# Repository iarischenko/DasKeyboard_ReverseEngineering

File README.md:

# Das Keyboard Model S

CST-104-DAS_Mother PCB  reverse engineering:\
- layout is the same as in original board, the original CST-104-DAS_Daughter
PCB Ver 1.5 could be used
- added hotswap Kailh sockets

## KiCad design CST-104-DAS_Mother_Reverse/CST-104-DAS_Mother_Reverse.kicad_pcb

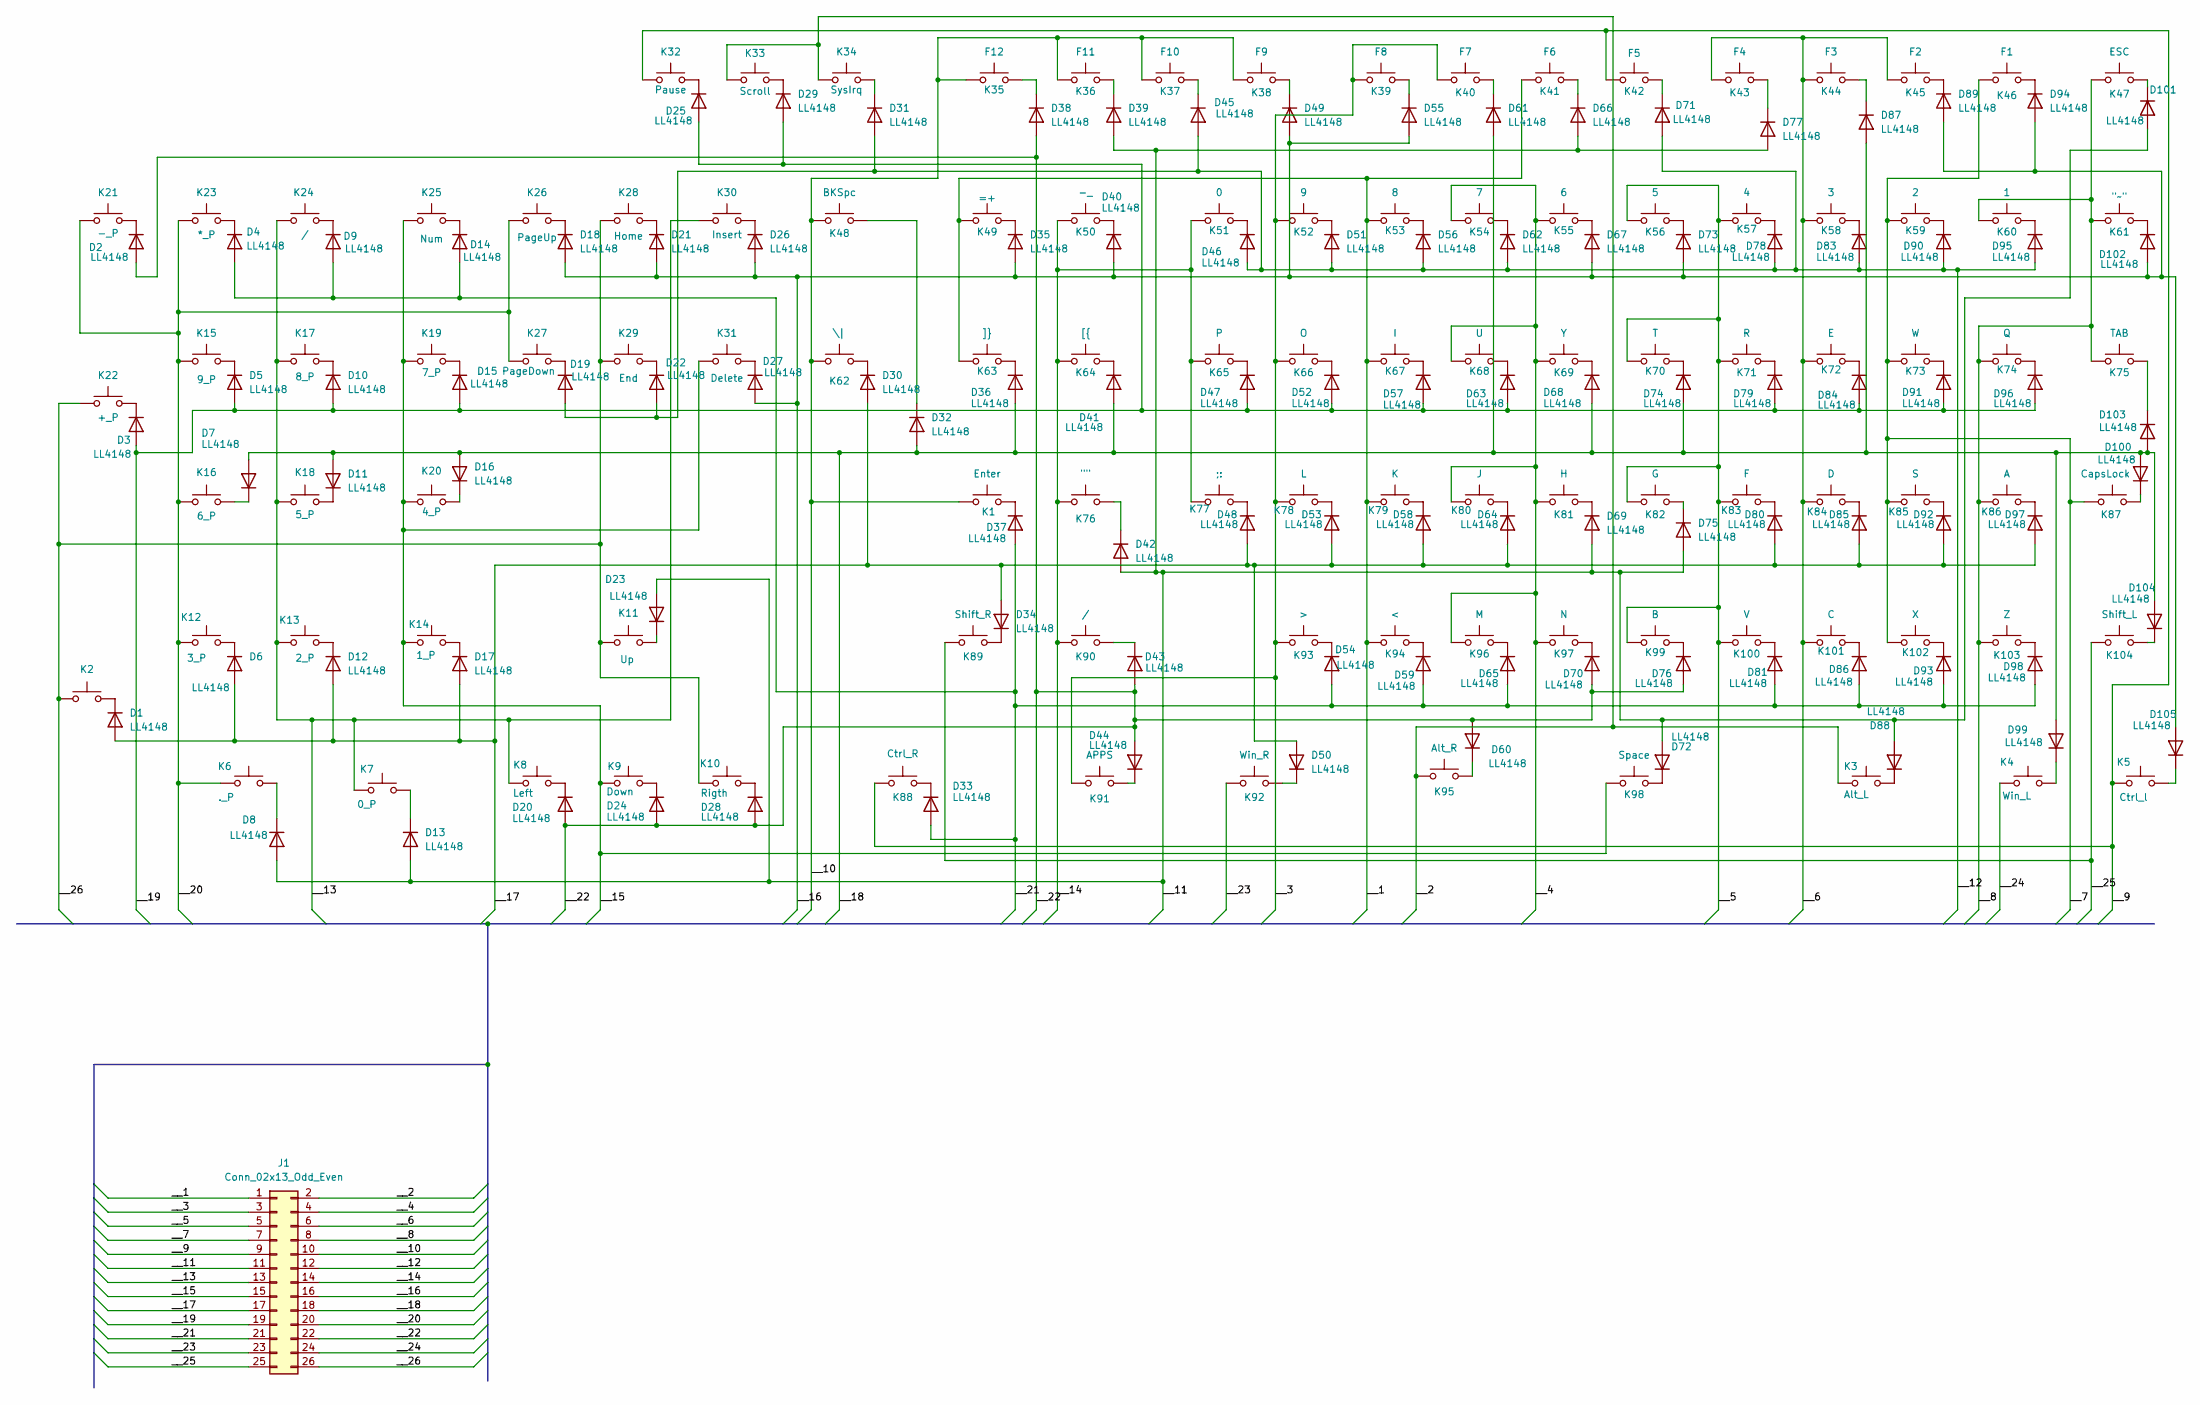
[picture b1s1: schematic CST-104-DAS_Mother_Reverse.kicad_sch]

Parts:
D1, D2, D3, D4, D5, D6, D7, D8, D9, D10, D11, D12, D13, D14, D15, D16, D17, D18, D19, D20, D21, D22, D23, D24, D25, D26, D27, D28, D29, D30, D31, D32, D33, D34, D35, D36, D37, D38, D39, D40, D41, D42, D43, D44, D45, D46, D47, D48, D49, D50, D51, D52, D53, D54, D55, D56, D57, D58, D59, D60, D61, D62, D63, D64, D65, D66, D67, D68, D69, D70, D71, D72, D73, D74, D75, D76, D77, D78, D79, D80, D81, D83, D84, D85, D86, D87, D88, D89, D90, D91, D92, D93, D94, D95, D96, D97, D98, D99, D100, D101, D102, D103, D104, D105: LL4148; D_MiniMELF
J1: Conn_02x13_Odd_Even; PinSocket_2x13_P2.54mm_Vertical
K1: Enter; SW_Hotswap_Kailh_MX
K2: Enter_P; SW_Hotswap_Kailh_MX
K3: Alt_L; SW_Hotswap_Kailh_MX
K4: Win_L; SW_Hotswap_Kailh_MX
K5: Ctrl_l; SW_Hotswap_Kailh_MX
K6: ._P; SW_Hotswap_Kailh_MX
K7: 0_P; SW_Hotswap_Kailh_MX
K8: Left; SW_Hotswap_Kailh_MX
K9: Down; SW_Hotswap_Kailh_MX
K10: Rigth; SW_Hotswap_Kailh_MX
K11: Up; SW_Hotswap_Kailh_MX
K12: 3_P; SW_Hotswap_Kailh_MX
K13: 2_P; SW_Hotswap_Kailh_MX
K14: 1_P; SW_Hotswap_Kailh_MX
K15: 9_P; SW_Hotswap_Kailh_MX
K16: 6_P; SW_Hotswap_Kailh_MX
K17: 8_P; SW_Hotswap_Kailh_MX
K18: 5_P; SW_Hotswap_Kailh_MX
K19: 7_P; SW_Hotswap_Kailh_MX
K20: 4_P; SW_Hotswap_Kailh_MX
K21: -_P; SW_Hotswap_Kailh_MX
K22: +_P; SW_Hotswap_Kailh_MX
K23: *_P; SW_Hotswap_Kailh_MX
K24, K90: /; SW_Hotswap_Kailh_MX
K25: Num; SW_Hotswap_Kailh_MX
K26: PageUp; SW_Hotswap_Kailh_MX
K27: PageDown; SW_Hotswap_Kailh_MX
K28: Home; SW_Hotswap_Kailh_MX
K29: End; SW_Hotswap_Kailh_MX
K30: Insert; SW_Hotswap_Kailh_MX
K31: Delete; SW_Hotswap_Kailh_MX
K32: Pause; SW_Hotswap_Kailh_MX
K33: Scroll; SW_Hotswap_Kailh_MX
K34: SysIrq; SW_Hotswap_Kailh_MX
K35: F12; SW_Hotswap_Kailh_MX
K36: F11; SW_Hotswap_Kailh_MX
K37: F10; SW_Hotswap_Kailh_MX
K38: F9; SW_Hotswap_Kailh_MX
K39: F8; SW_Hotswap_Kailh_MX
K40: F7; SW_Hotswap_Kailh_MX
K41: F6; SW_Hotswap_Kailh_MX
K42: F5; SW_Hotswap_Kailh_MX
K43: F4; SW_Hotswap_Kailh_MX
K44: F3; SW_Hotswap_Kailh_MX
K45: F2; SW_Hotswap_Kailh_MX
K46: F1; SW_Hotswap_Kailh_MX
K47: ESC; SW_Hotswap_Kailh_MX
K48: BKSpc; SW_Hotswap_Kailh_MX
K49: =+; SW_Hotswap_Kailh_MX
K50: -_; SW_Hotswap_Kailh_MX
K51: 0; SW_Hotswap_Kailh_MX
K52: 9; SW_Hotswap_Kailh_MX
K53: 8; SW_Hotswap_Kailh_MX
K54: 7; SW_Hotswap_Kailh_MX
K55: 6; SW_Hotswap_Kailh_MX
K56: 5; SW_Hotswap_Kailh_MX
K57: 4; SW_Hotswap_Kailh_MX
K58: 3; SW_Hotswap_Kailh_MX
K59: 2; SW_Hotswap_Kailh_MX
K60: 1; SW_Hotswap_Kailh_MX
K61: "~"; SW_Hotswap_Kailh_MX
K62: \|; SW_Hotswap_Kailh_MX
K63: ]}; SW_Hotswap_Kailh_MX
K64: [{; SW_Hotswap_Kailh_MX
K65: P; SW_Hotswap_Kailh_MX
K66: O; SW_Hotswap_Kailh_MX
K67: I; SW_Hotswap_Kailh_MX
K68: U; SW_Hotswap_Kailh_MX
K69: Y; SW_Hotswap_Kailh_MX
K70: T; SW_Hotswap_Kailh_MX
K71: R; SW_Hotswap_Kailh_MX
K72: E; SW_Hotswap_Kailh_MX
K73: W; SW_Hotswap_Kailh_MX
K74: Q; SW_Hotswap_Kailh_MX
K75: TAB; SW_Hotswap_Kailh_MX
K76: ""; SW_Hotswap_Kailh_MX
K77: ;:; SW_Hotswap_Kailh_MX
K78: L; SW_Hotswap_Kailh_MX
K79: K; SW_Hotswap_Kailh_MX
K80: J; SW_Hotswap_Kailh_MX
K81: H; SW_Hotswap_Kailh_MX
K82: G; SW_Hotswap_Kailh_MX
K83: F; SW_Hotswap_Kailh_MX
K84: D; SW_Hotswap_Kailh_MX
K85: S; SW_Hotswap_Kailh_MX
K86: A; SW_Hotswap_Kailh_MX
K87: CapsLock; SW_Hotswap_Kailh_MX
K88: Ctrl_R; SW_Hotswap_Kailh_MX
K89: Shift_R; SW_Hotswap_Kailh_MX
K91: APPS; SW_Hotswap_Kailh_MX
K92: Win_R; SW_Hotswap_Kailh_MX
K93: >; SW_Hotswap_Kailh_MX
K94: <; SW_Hotswap_Kailh_MX
K95: Alt_R; SW_Hotswap_Kailh_MX
K96: M; SW_Hotswap_Kailh_MX
K97: N; SW_Hotswap_Kailh_MX
K98: Space; SW_Hotswap_Kailh_MX
K99: B; SW_Hotswap_Kailh_MX
K100: V; SW_Hotswap_Kailh_MX
K101: C; SW_Hotswap_Kailh_MX
K102: X; SW_Hotswap_Kailh_MX
K103: Z; SW_Hotswap_Kailh_MX
K104: Shift_L; SW_Hotswap_Kailh_MX

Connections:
/__1: J1.1, K41.1, K49.1, K53.1, K63.1, K67.1, K79.1, K94.1
/__2: J1.2, K3.1, K33.1, K34.1, K95.1
/__3: J1.3, K39.1, K40.1, K52.1, K66.1, K78.1, K91.1, K93.1
/__4: J1.4, K54.1, K55.1, K68.1, K69.1, K80.1, K81.1, K96.1, K97.1
/__5: J1.5, K56.1, K57.1, K70.1, K71.1, K82.1, K83.1, K99.1, K100.1
/__6: J1.6, K43.1, K44.1, K45.1, K58.1, K72.1, K84.1, K101.1
/__7: J1.7, K46.1, K59.1, K73.1, K85.1, K87.1, K102.1
/__8: J1.8, K47.1, K60.1, K61.1, K74.1, K75.1, K86.1, K103.1
/__9: J1.9, K5.1, K32.1, K42.1, K88.1
/__10: J1.10, K1.1, K35.1, K36.1, K37.1, K38.1, K48.1, K62.1
/__11: D8.2 (A), D13.2 (A), D23.2 (A), D39.2 (A), D42.2 (A), D66.2 (A), D69.2 (A), D72.2 (A), D75.2 (A), D77.2 (A), D88.2 (A), D101.2 (A), J1.11
/__12: D19.2 (A), D22.2 (A), D31.2 (A), D45.2 (A), D46.2 (A), D51.2 (A), D56.2 (A), D62.2 (A), D71.2 (A), D78.2 (A), D83.2 (A), D90.2 (A), D95.2 (A), J1.12
/__13: J1.13, K7.1, K8.1, K13.1, K17.1, K18.1, K24.1, K30.1
/__14: J1.14, K50.1, K51.1, K64.1, K65.1, K76.1, K77.1, K90.1
/__15: J1.15, K9.1, K14.1, K19.1, K20.1, K25.1, K31.1, K98.1
/__16: D18.2 (A), D21.2 (A), D26.2 (A), D27.2 (A), D35.2 (A), D40.2 (A), D49.2 (A), D55.2 (A), D67.2 (A), D73.2 (A), D89.2 (A), D94.2 (A), D102.2 (A), D105.2 (A), J1.16
/__17: D1.2 (A), D6.2 (A), D12.2 (A), D17.2 (A), D30.2 (A), D34.2 (A), D48.2 (A), D50.2 (A), D53.2 (A), D58.2 (A), D64.2 (A), D80.2 (A), D85.2 (A), D92.2 (A), D97.2 (A), J1.17
/__18: D7.2 (A), D11.2 (A), D16.2 (A), D32.2 (A), D36.2 (A), D41.2 (A), D61.2 (A), D68.2 (A), D74.2 (A), D87.2 (A), D99.2 (A), D100.2 (A), D103.2 (A), D104.2 (A), J1.18
/__19: D3.2 (A), D5.2 (A), D10.2 (A), D15.2 (A), D25.2 (A), D29.2 (A), D47.2 (A), D52.2 (A), D57.2 (A), D63.2 (A), D79.2 (A), D84.2 (A), D91.2 (A), D96.2 (A), J1.19
/__20: J1.20, K6.1, K12.1, K15.1, K16.1, K21.1, K23.1, K26.1, K27.1
/__21: D4.2 (A), D9.2 (A), D14.2 (A), D33.2 (A), D37.2 (A), D54.2 (A), D59.2 (A), D65.2 (A), D81.2 (A), D86.2 (A), D93.2 (A), D98.2 (A), J1.21
/__22: D2.2 (A), D20.2 (A), D24.2 (A), D28.2 (A), D38.2 (A), D43.2 (A), D44.2 (A), D60.2 (A), D70.2 (A), D76.2 (A), J1.22
/__23: J1.23, K92.1
/__24: J1.24, K4.1
/__25: J1.25, K89.1, K104.1
/__26: J1.26, K2.1, K10.1, K11.1, K22.1, K28.1, K29.1
unnamed: D1.1 (K), K2.2
unnamed: D2.1 (K), K21.2
unnamed: D3.1 (K), K22.2
unnamed: D4.1 (K), K23.2
unnamed: D5.1 (K), K15.2
unnamed: D6.1 (K), K12.2
unnamed: D7.1 (K), K16.2
unnamed: D8.1 (K), K6.2
unnamed: D9.1 (K), K24.2
unnamed: D10.1 (K), K17.2
unnamed: D11.1 (K), K18.2
unnamed: D12.1 (K), K13.2
unnamed: D13.1 (K), K7.2
unnamed: D14.1 (K), K25.2
unnamed: D15.1 (K), K19.2
unnamed: D16.1 (K), K20.2
unnamed: D17.1 (K), K14.2
unnamed: D18.1 (K), K26.2
unnamed: D19.1 (K), K27.2
unnamed: D20.1 (K), K8.2
unnamed: D21.1 (K), K28.2
unnamed: D22.1 (K), K29.2
unnamed: D23.1 (K), K11.2
unnamed: D24.1 (K), K9.2
unnamed: D25.1 (K), K32.2
unnamed: D26.1 (K), K30.2
unnamed: D27.1 (K), K31.2
unnamed: D28.1 (K), K10.2
unnamed: D29.1 (K), K33.2
unnamed: D30.1 (K), K62.2
unnamed: D31.1 (K), K34.2
unnamed: D32.1 (K), K48.2
unnamed: D33.1 (K), K88.2
unnamed: D34.1 (K), K89.2
unnamed: D35.1 (K), K49.2
unnamed: D36.1 (K), K63.2
unnamed: D37.1 (K), K1.2
unnamed: D38.1 (K), K35.2
unnamed: D39.1 (K), K36.2
unnamed: D40.1 (K), K50.2
unnamed: D41.1 (K), K64.2
unnamed: D42.1 (K), K76.2
unnamed: D43.1 (K), K90.2
unnamed: D44.1 (K), K91.2
unnamed: D45.1 (K), K37.2
unnamed: D46.1 (K), K51.2
unnamed: D47.1 (K), K65.2
unnamed: D48.1 (K), K77.2
unnamed: D49.1 (K), K38.2
unnamed: D50.1 (K), K92.2
unnamed: D51.1 (K), K52.2
unnamed: D52.1 (K), K66.2
unnamed: D53.1 (K), K78.2
unnamed: D54.1 (K), K93.2
unnamed: D55.1 (K), K39.2
unnamed: D56.1 (K), K53.2
unnamed: D57.1 (K), K67.2
unnamed: D58.1 (K), K79.2
unnamed: D59.1 (K), K94.2
unnamed: D60.1 (K), K95.2
unnamed: D61.1 (K), K40.2
unnamed: D62.1 (K), K54.2
unnamed: D63.1 (K), K68.2
unnamed: D64.1 (K), K80.2
unnamed: D65.1 (K), K96.2
unnamed: D66.1 (K), K41.2
unnamed: D67.1 (K), K55.2
unnamed: D68.1 (K), K69.2
unnamed: D69.1 (K), K81.2
unnamed: D70.1 (K), K97.2
unnamed: D71.1 (K), K42.2
unnamed: D72.1 (K), K98.2
unnamed: D73.1 (K), K56.2
unnamed: D74.1 (K), K70.2
unnamed: D75.1 (K), K82.2
unnamed: D76.1 (K), K99.2
unnamed: D77.1 (K), K43.2
unnamed: D78.1 (K), K57.2
unnamed: D79.1 (K), K71.2
unnamed: D80.1 (K), K83.2
unnamed: D81.1 (K), K100.2
unnamed: D83.1 (K), K58.2
unnamed: D84.1 (K), K72.2
unnamed: D85.1 (K), K84.2
unnamed: D86.1 (K), K101.2
unnamed: D87.1 (K), K44.2
unnamed: D88.1 (K), K3.2
unnamed: D89.1 (K), K45.2
unnamed: D90.1 (K), K59.2
unnamed: D91.1 (K), K73.2
unnamed: D92.1 (K), K85.2
unnamed: D93.1 (K), K102.2
unnamed: D94.1 (K), K46.2
unnamed: D95.1 (K), K60.2
unnamed: D96.1 (K), K74.2
unnamed: D97.1 (K), K86.2
unnamed: D98.1 (K), K103.2
unnamed: D99.1 (K), K4.2
unnamed: D100.1 (K), K87.2
unnamed: D101.1 (K), K47.2
unnamed: D102.1 (K), K61.2
unnamed: D103.1 (K), K75.2
unnamed: D104.1 (K), K104.2
unnamed: D105.1 (K), K5.2

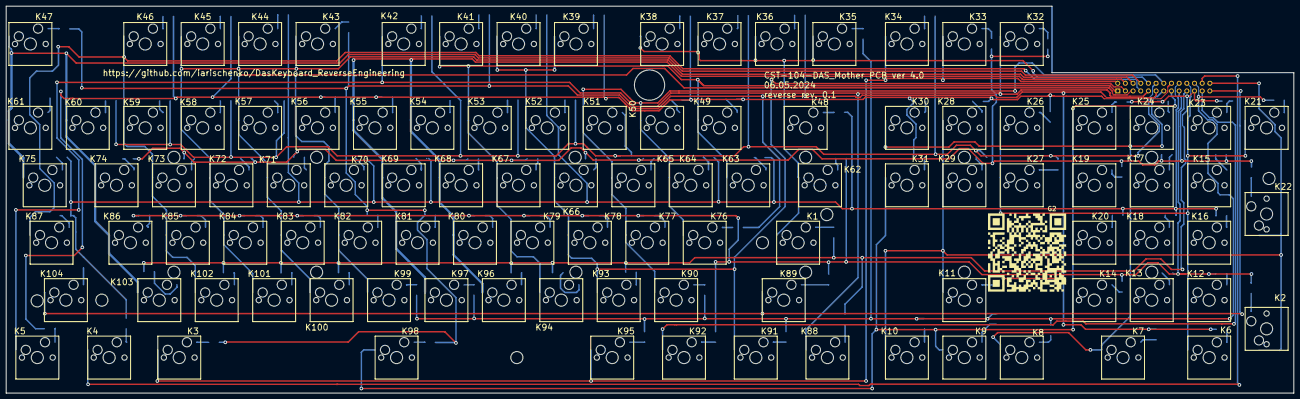
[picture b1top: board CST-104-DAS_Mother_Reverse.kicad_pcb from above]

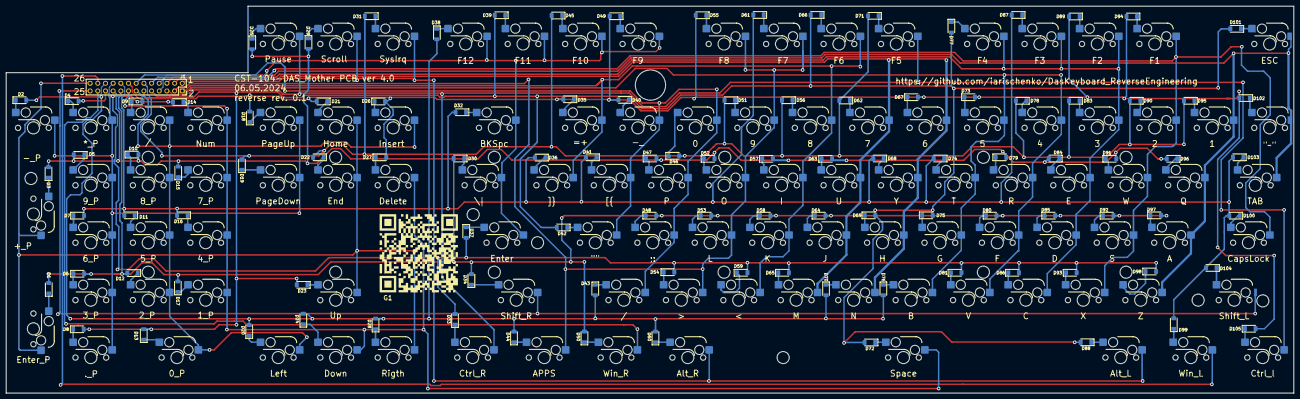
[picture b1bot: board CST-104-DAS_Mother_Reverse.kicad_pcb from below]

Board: 2 copper layers, 426.0 x 128.0 mm, 211 parts (106 on the bottom side), 130 nets.

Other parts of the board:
G1, G2: LOGO

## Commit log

2024-05-01 DAS Keyboard S: initial commit
    Added kicad project:
    - mother board shematic
    - pcb initial version
2024-05-07 revision 0.1 is oredered!
    update:
    - sch is updated
    - pcb is updated and traced
    - fabrical output is created and sent to production
    (ETA: 1 month)
